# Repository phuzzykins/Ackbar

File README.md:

# Ackbar's Snack Bar

A new rat trap design

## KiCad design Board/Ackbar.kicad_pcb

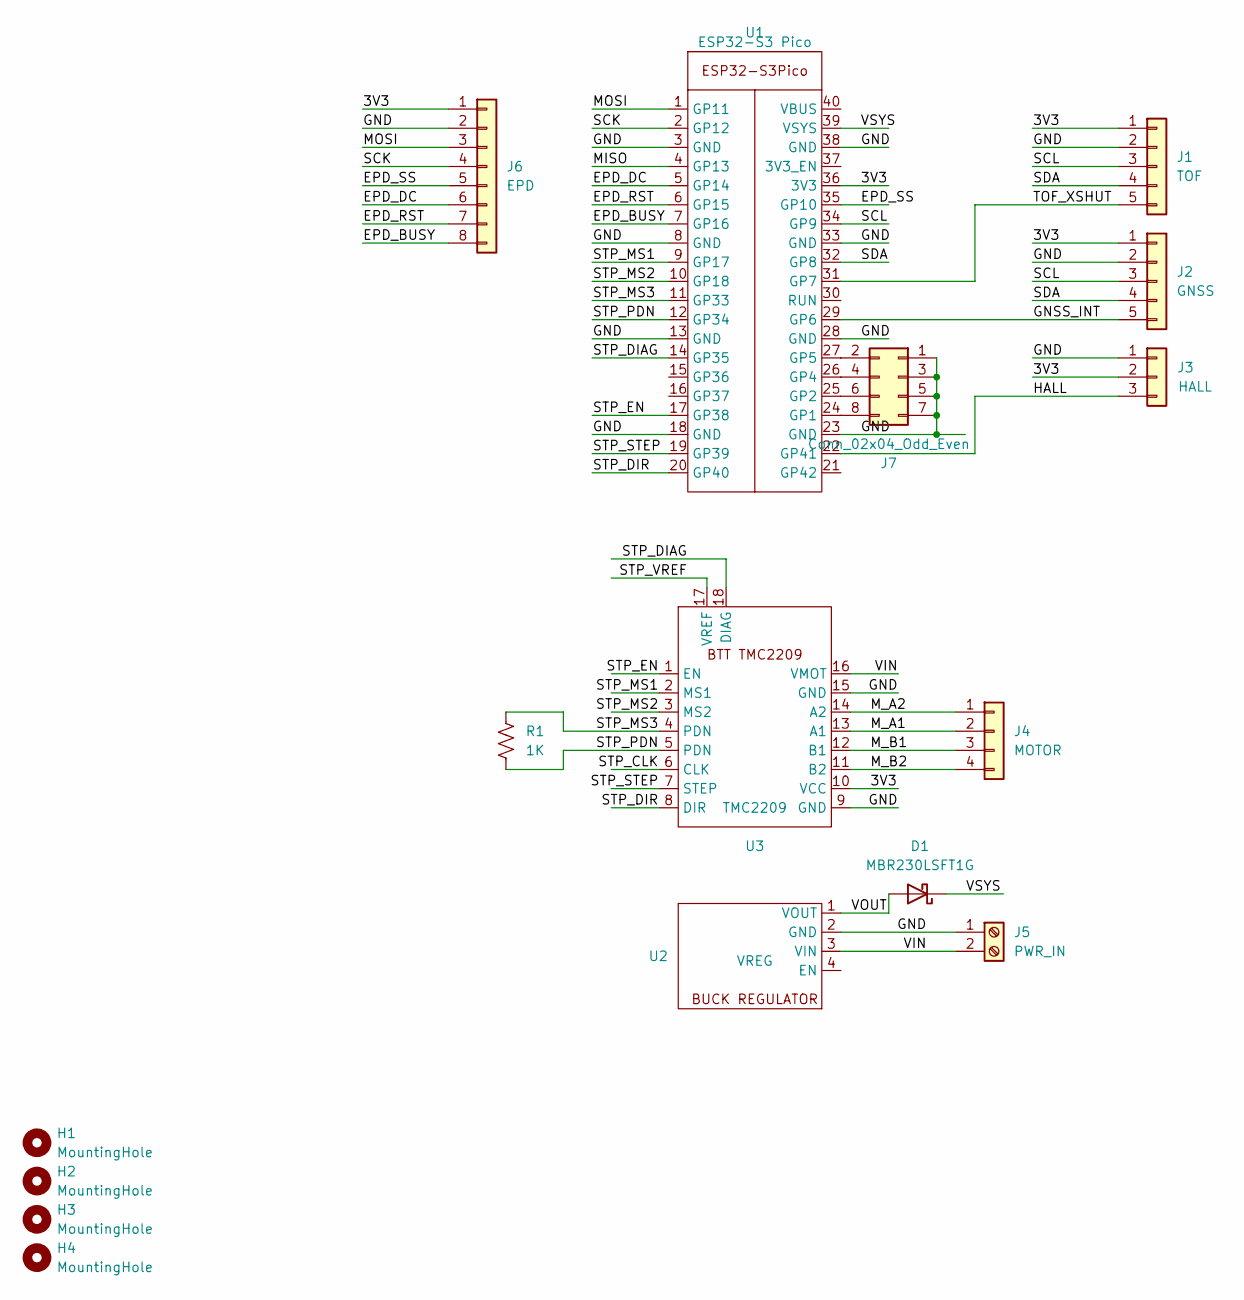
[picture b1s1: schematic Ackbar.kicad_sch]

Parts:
D1: MBR230LSFT1G; D_SOD-123
H1, H2, H3, H4: MountingHole; MountingHole_3.2mm_M3
J1: TOF; 1X05
J2: GNSS; 1X05
J3: HALL; 1X03
J4: MOTOR; 1X04
J5: PWR_IN; TerminalBlock_4Ucon_1x02_P3.50mm_Horizontal
J6: EPD; 1X08
J7: Conn_02x04_Odd_Even; PinSocket_2x04_P2.54mm_Vertical
R1: 1K; R_0805_2012Metric_Pad1.20x1.40mm_HandSolder
U1: ESP32-S3 Pico; Waveshare ESP32-S3 Pico
U2: VREG; Buck Regulator
U3: TMC2209; BTT TMC2209

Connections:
/3V3: J1.1, J2.1, J3.2, J6.1, U1.36 (3V3), U3.10 (VCC)
/EPD_BUSY: J6.8, U1.7 (GP16)
/EPD_DC: J6.6, U1.5 (GP14)
/EPD_RST: J6.7, U1.6 (GP15)
/EPD_SS: J6.5, U1.35 (GP10)
/GND: J1.2, J2.2, J3.1, J5.1, J6.2, J7.1, J7.3, J7.5, J7.7, U1.3 (GND), U1.8 (GND), U1.13 (GND), U1.18 (GND), U1.23 (GND), U1.28 (GND), U1.33 (GND), U1.38 (GND), U2.2 (GND), U3.9 (GND), U3.15 (GND)
/GNSS_INT: J2.5, U1.29 (GP6)
/HALL: J3.3, U1.22 (GP41)
/MISO: U1.4 (GP13)
/MOSI: J6.3, U1.1 (GP11)
/M_A1: J4.2, U3.13 (A1)
/M_A2: J4.1, U3.14 (A2)
/M_B1: J4.3, U3.12 (B1)
/M_B2: J4.4, U3.11 (B2)
/SCK: J6.4, U1.2 (GP12)
/SCL: J1.3, J2.3, U1.34 (GP9)
/SDA: J1.4, J2.4, U1.32 (GP8)
/STP_CLK: U3.6 (CLK)
/STP_DIAG: U1.14 (GP35), U3.18 (DIAG)
/STP_DIR: U1.20 (GP40), U3.8 (DIR)
/STP_EN: U1.17 (GP38), U3.1 (EN)
/STP_MS1: U1.9 (GP17), U3.2 (MS1)
/STP_MS2: U1.10 (GP18), U3.3 (MS2)
/STP_MS3: R1.1, U1.11 (GP33), U3.4 (PDN)
/STP_PDN: R1.2, U1.12 (GP34), U3.5 (PDN)
/STP_STEP: U1.19 (GP39), U3.7 (STEP)
/STP_VREF: U3.17 (VREF)
/TOF_XSHUT: J1.5, U1.31 (GP7)
/VIN: J5.2, U2.3 (VIN), U3.16 (VMOT)
/VOUT: D1.2 (A), U2.1 (VOUT)
/VSYS: D1.1 (K), U1.39 (VSYS)
unnamed: J7.2, U1.27 (GP5)
unnamed: J7.4, U1.26 (GP4)
unnamed: J7.6, U1.25 (GP2)
unnamed: J7.8, U1.24 (GP1)

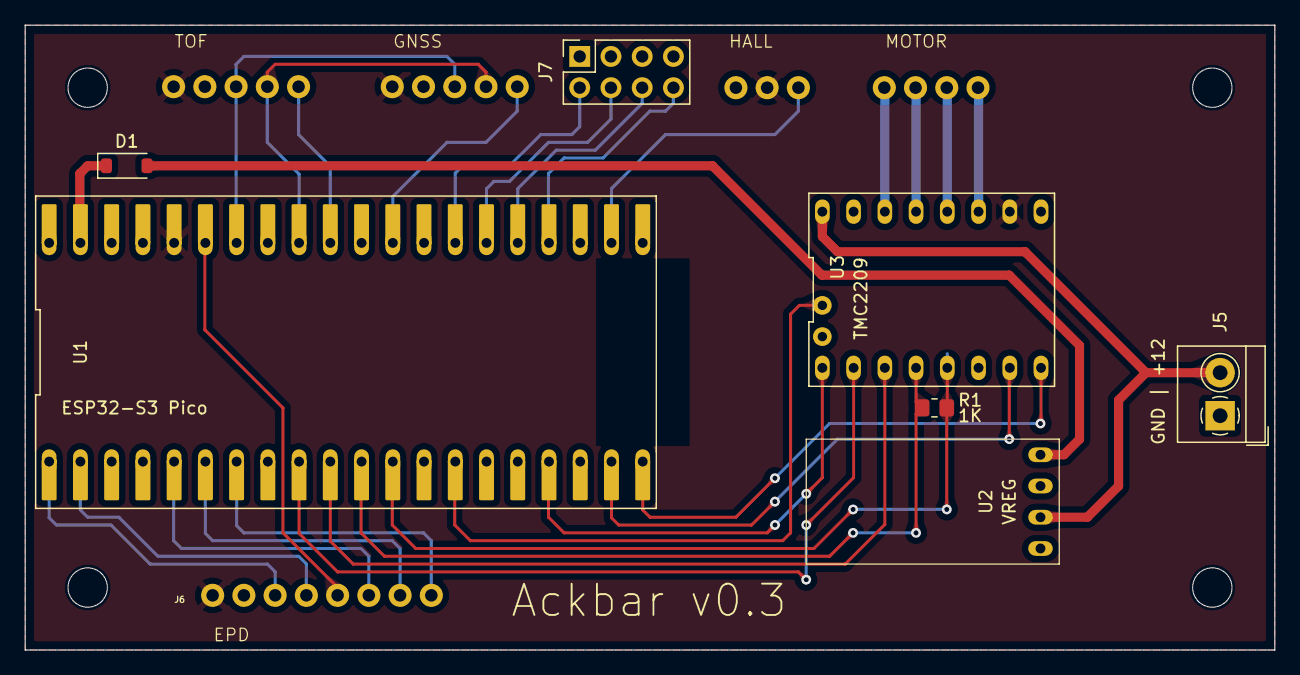
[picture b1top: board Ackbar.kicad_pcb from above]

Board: 2 copper layers, 101.6 x 50.8 mm, 16 parts (0 on the bottom side), 32 nets.

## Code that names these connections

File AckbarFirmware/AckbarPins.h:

#ifndef __ACKBAR_PINS_H__
#define __ACKBAR_PINS_H__

#include "Arduino.h"

#define STP_MS1   17
#define STP_MS2   18
#define STP_MS3   33
#define STP_PDN   34
#define STP_DIAG  35
#define STP_EN    38
#define STP_STEP  39
#define STP_DIR   40

#define STP_UART_TX  STP_MS3
#define STP_UART_RX  STP_PDN

#define EPD_DC    14
#define EPD_CS    10
#define EPD_BUSY  16
#define SRAM_CS   -1
#define EPD_RESET 15
#define EPD_SPI   &SPI

#define TOF_XSHUT 7

#define GNSS_INT  6

#define HALL      41

#define RGB_BUILTIN 21

#endif // __ACKBAR_PINS_H__

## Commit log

2023-09-18 Adding old version of firmware
2023-09-18 Cleanup
2023-09-18 Cleanup ground fill
2023-09-18 bvqaerfrethwbbtrwwrbet
2023-09-18 Clean up ESP32 footprint to merge pads properly
2023-09-18 regenerate fills
2023-09-19 Adding BOM
2023-09-19 Remove autogenerated dir
2023-09-19 update bom
2023-09-20 add inverter to schematic
2023-09-20 Larger footprint for inverter
2023-09-21 cleanup vreg inhibit
2023-09-22 Re-route PCB and move USB C connector to board edge
2023-09-22 WIP of firmware refactoring
2023-09-23 WIP of refactoring
2023-09-24 Refactoring WIP - Plumbing works!
2023-09-24 WIP of refactoring - basic functionality tested on hardware
2023-09-24 Refactoring is now functionally equivalent to legacy firmware
2023-09-24 Removing legacy firmware
2023-09-24 Break out event distribution to make it easier for components to send events without getting the controller class involved
2023-09-24 Move events to their own thread
2023-09-24 Exclude kicad library backups
2023-09-24 Switch to native esp32 / freeRTOS task API to pin event thread to opposite core of Arduino
2023-09-24 Whoops, event thread needs more stack space when wifi is required
2023-09-24 Still not enough stack
2023-09-24 Prep work for further ePaper display development - add a few more events, and get the blocking device writes into the event thread
2023-09-24 Remove unnecessary lock during iteration over eventConsumers; this isn't allowed to change at runtime anyway and was causing deadlocks with sending events from within event handlers.
2023-09-24 Add synchronous delivery option for event consumers to avoid LED updates getting stuck behind ePaper and network operations
2023-09-24 Add pullup resistor to vreg enable
2023-09-24 Okay, you win, we're using the onboard regulator
2023-09-24 Ignore more generated crap
2023-09-24 Replace missing mounting holes
2023-09-25 Switch to GxEPD2 ePaper driver as the Adafruit one is not well maintained
2023-09-25 QR code support
2023-09-26 Very minor cleanup to use min() and make it explicit what we're doing when we're using a generically named method from a superclass
2023-09-29 Switch to HTTPS for notifications, and keep track of notifications we were unable to send.
2023-10-01 Adding basic Bluetooth LE functionality
2023-10-07 Add error handling to begin and calibrate methods
2023-10-07 Push errors to the e-ink display
2023-10-12 Version sent to MTM
2023-10-26 Add delay time
2023-11-06 Enjoy the STLs
2023-11-08 add user's guide
2023-11-10 Modify the chute parts to slide into the t-slots rather than use fasteners
2023-11-13 Break out a few currently unused pins for config jumpers
2023-11-30 Add alignment dimples to the planetary bearings, and teardrop the motor boss cutout
